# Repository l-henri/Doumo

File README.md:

# Doumo

This repository contains the hardware and software files for the Doumo project i.e. a GSM based connected object that create a lightshow when receiving a SMS.

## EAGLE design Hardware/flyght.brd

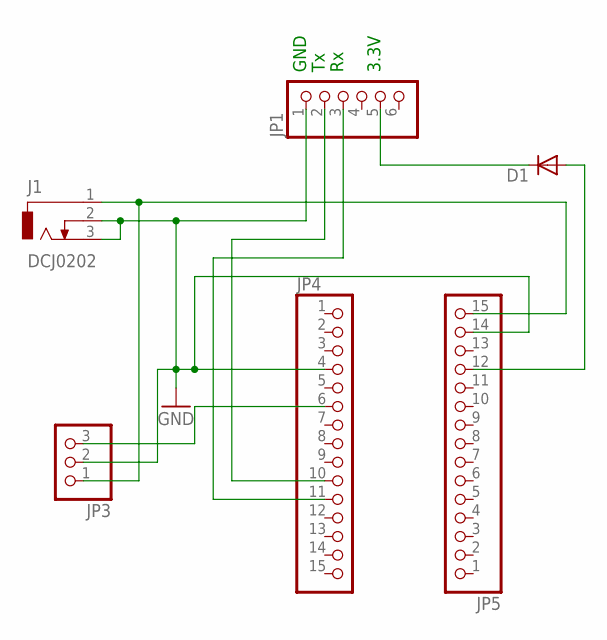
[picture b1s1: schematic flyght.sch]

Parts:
D1: 1N4004; DO41-10
J1: DCJ0202
JP1: PINHD-1X6; 1X06
JP3: PINHD-1X3; 1X03
JP4, JP5: PINHD-1X15; 1X15

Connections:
GND: J1.2, J1.3, JP1.1, JP3.2, JP4.4, JP5.14
LED_DATA: JP3.3, JP4.6
unnamed: D1.C, JP1.5
unnamed: D1.A, JP5.12
unnamed: JP1.3, JP4.11
unnamed: JP1.2, JP4.10
VCC: J1.1, JP3.1, JP5.15

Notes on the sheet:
GND
3.3V

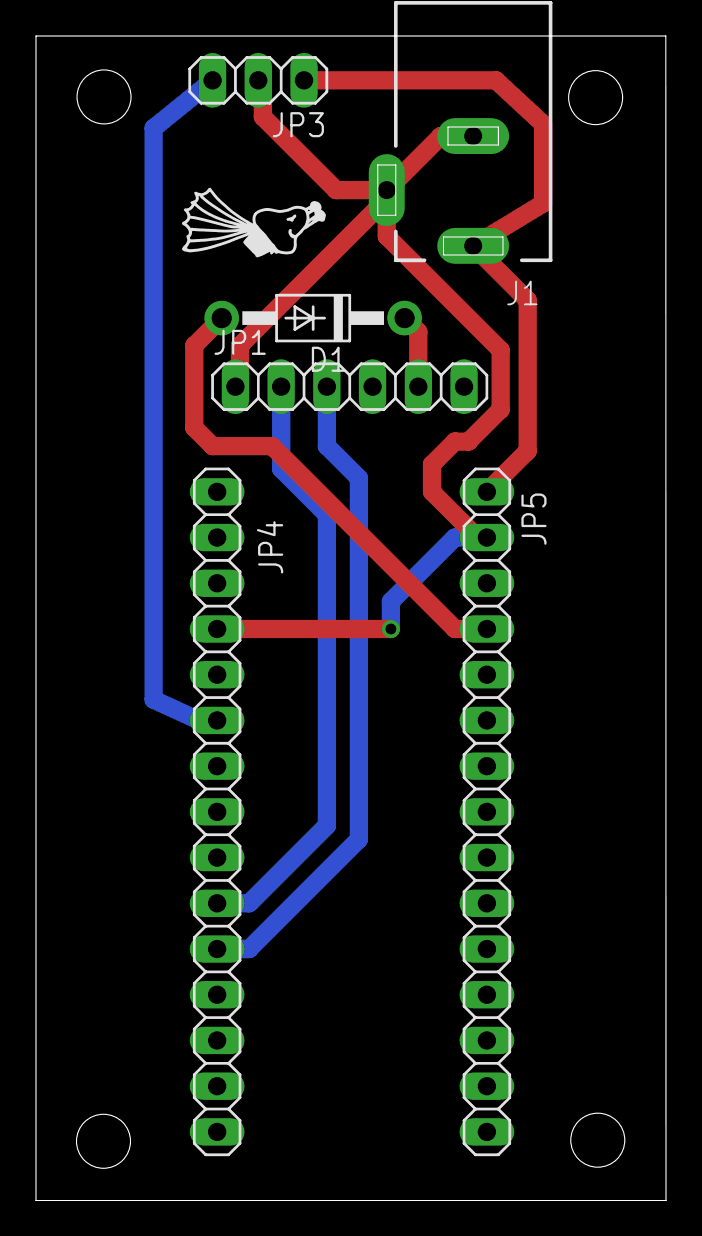
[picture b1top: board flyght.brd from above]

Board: 2 copper layers, 35.0 x 64.7 mm, 6 parts (0 on the bottom side), 7 nets.

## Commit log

2016-10-23 Initial file
2016-10-23 Added whole file + Led management in 02_ledAnimation
2016-10-23 Led management done
2016-10-23 Starting from SMS response sketch
2016-10-24 With automation
2016-10-24 Integrated SMS receive + Star generation
2018-10-17 Not sure what I am committing but eh
2018-12-08 Create Reamde, add hardware files and move files into folders.
2018-12-18 Renamed files, added SVG image source, created version with copper pour if needed
2019-03-14 Added new files
2019-03-18 Edited program slightly to add more delays
2019-05-03 Changed project name
